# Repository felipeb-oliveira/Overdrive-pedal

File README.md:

# Overdrive-pedal

## About
A simple overdrive circuit implemented with a OpAmp with soft clipping and a tone control. The OpAmp is configured as a non-inverting amplifier supplied with +9V and GND, with a 4.5V DC bias. The circuit is separated in 5 stages (see schematic image below the 3D model):
  1. Input: one Mono jack for audio;
  2. Equalization: capacitors to filter out some low noise and DC;
  3. Gain stage with soft clipping (made by the 2 opposed diodes on the OpAmp feedback) and low pass filter (capacitor on the OpAmp feedback, and grounded capacitor and resistor on the OpAmp negative input);
  4. Tone Control (Inpired by the Big Muff tone control circuit): basicaly a low pass filter in parallel with a high pass filter, united by a potentiometer to control the filtering.
  5. BJT buffer
  6. Output with volume control: a grounded potentiometer, where the output can be controlled from GND to the total distorced signal.

## Overdrive Schematic
*This is only the soft clipping and tone control circuit, without the inputs, outputs and supply circuits. Please open the Altium project for the full circuit.*

## Board

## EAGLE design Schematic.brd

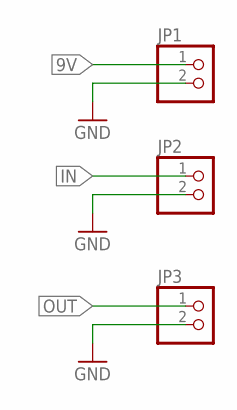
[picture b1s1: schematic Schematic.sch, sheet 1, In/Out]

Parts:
JP1, JP2, JP3: PINHD-1X2; 1X02

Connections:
9V: JP1.1; also elsewhere on the board
GND: JP1.2, JP2.2, JP3.2; also elsewhere on the board
IN: JP2.1; also elsewhere on the board
OUT: JP3.1; also elsewhere on the board

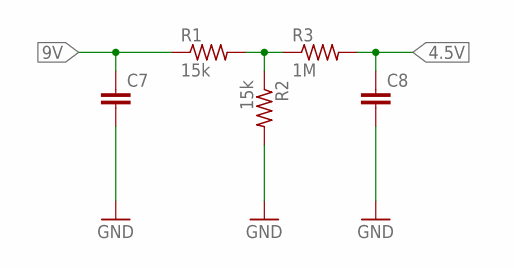
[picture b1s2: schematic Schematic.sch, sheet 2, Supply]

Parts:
C7, C8: C-EU025-025X050; C025-025X050
R1, R2: 15k; 0204/7
R3: 1M; 0204/7

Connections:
4.5V: C8.1, R3.2; also elsewhere on the board
9V: C7.1, R1.1; also elsewhere on the board
GND: C7.2, C8.2, R2.2; also elsewhere on the board
unnamed: R1.2, R2.1, R3.1

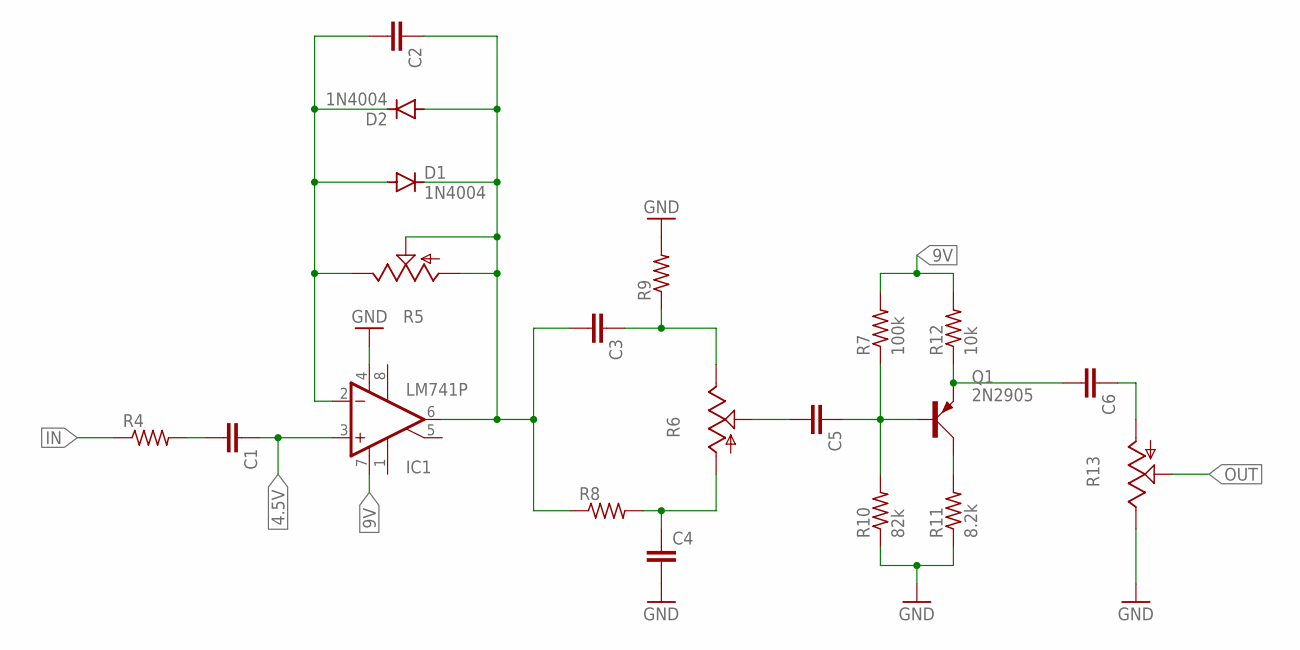
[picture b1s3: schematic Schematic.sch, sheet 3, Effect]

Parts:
C1, C2, C3, C4, C5, C6: C-EU025-025X050; C025-025X050
D1, D2: 1N4004; DO41-10
IC1: LM741P; DIL08
Q1: 2N2905; TO39
R4, R8, R9: R-US_0204/7; 0204/7
R5, R6, R13: TRIM_US-B64Y; B64Y
R7: 100k; 0204/7
R10: 82k; 0204/7
R11: 8.2k; 0204/7
R12: 10k; 0204/7

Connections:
4.5V: C1.1, IC1.3 (+IN); also elsewhere on the board
9V: IC1.7 (V+), R7.2, R12.2; also elsewhere on the board
GND: C4.2, IC1.4 (V-), R9.2, R10.1, R11.1, R13.E; also elsewhere on the board
IN: R4.1; also elsewhere on the board
unnamed: C1.2, R4.2
unnamed: C2.1, C3.2, D1.C, D2.A, IC1.6 (OUT), R5.A, R5.S, R8.1
unnamed: C2.2, D1.A, D2.C, IC1.2 (-IN), R5.E
unnamed: C3.1, R6.E, R9.1
unnamed: C4.1, R6.A, R8.2
unnamed: C5.2, R6.S
unnamed: C5.1, Q1.2 (B), R7.1, R10.2
unnamed: C6.2, Q1.1 (E), R12.1
unnamed: Q1.3 (C), R11.2
unnamed: C6.1, R13.A
OUT: R13.S; also elsewhere on the board

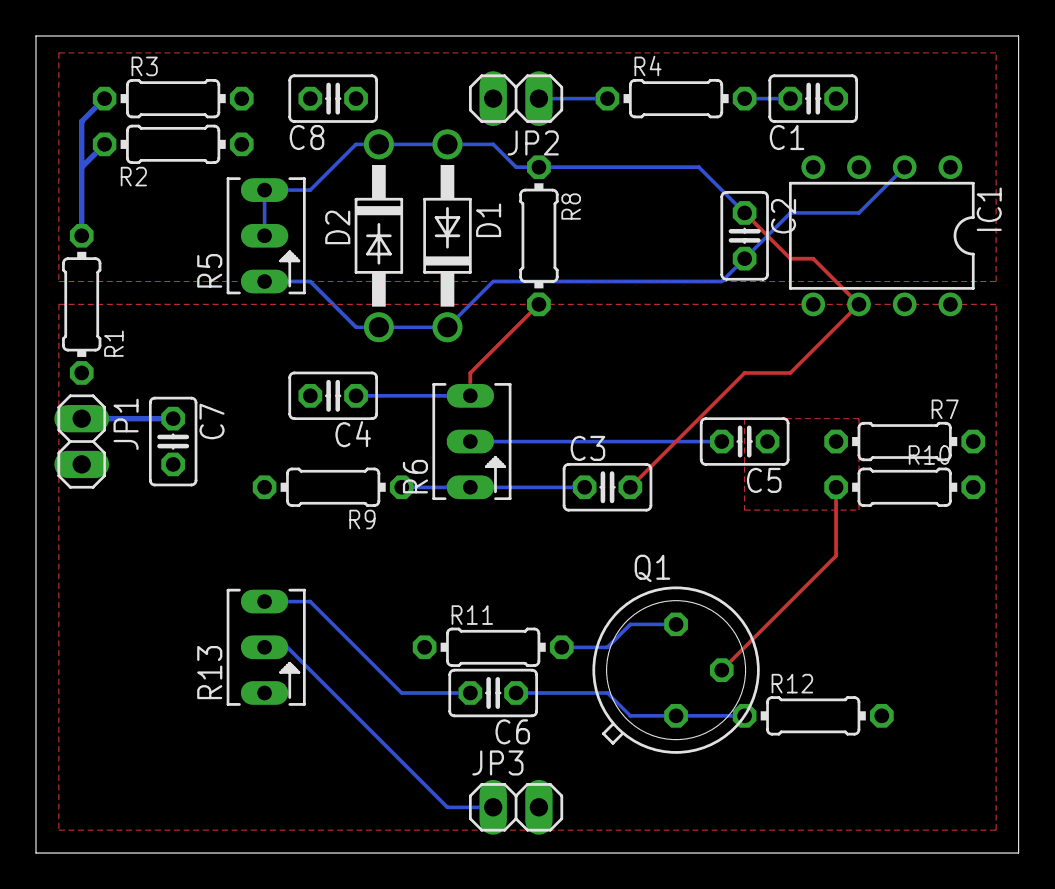
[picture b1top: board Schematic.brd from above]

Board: 2 copper layers, 54.6 x 45.4 mm, 28 parts (0 on the bottom side), 16 nets.

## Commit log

2021-08-15 Updated project
2021-08-15 Included readme
